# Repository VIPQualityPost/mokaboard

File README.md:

# mokaboard
A custom mechanical keyboard that is suited to my preferences.

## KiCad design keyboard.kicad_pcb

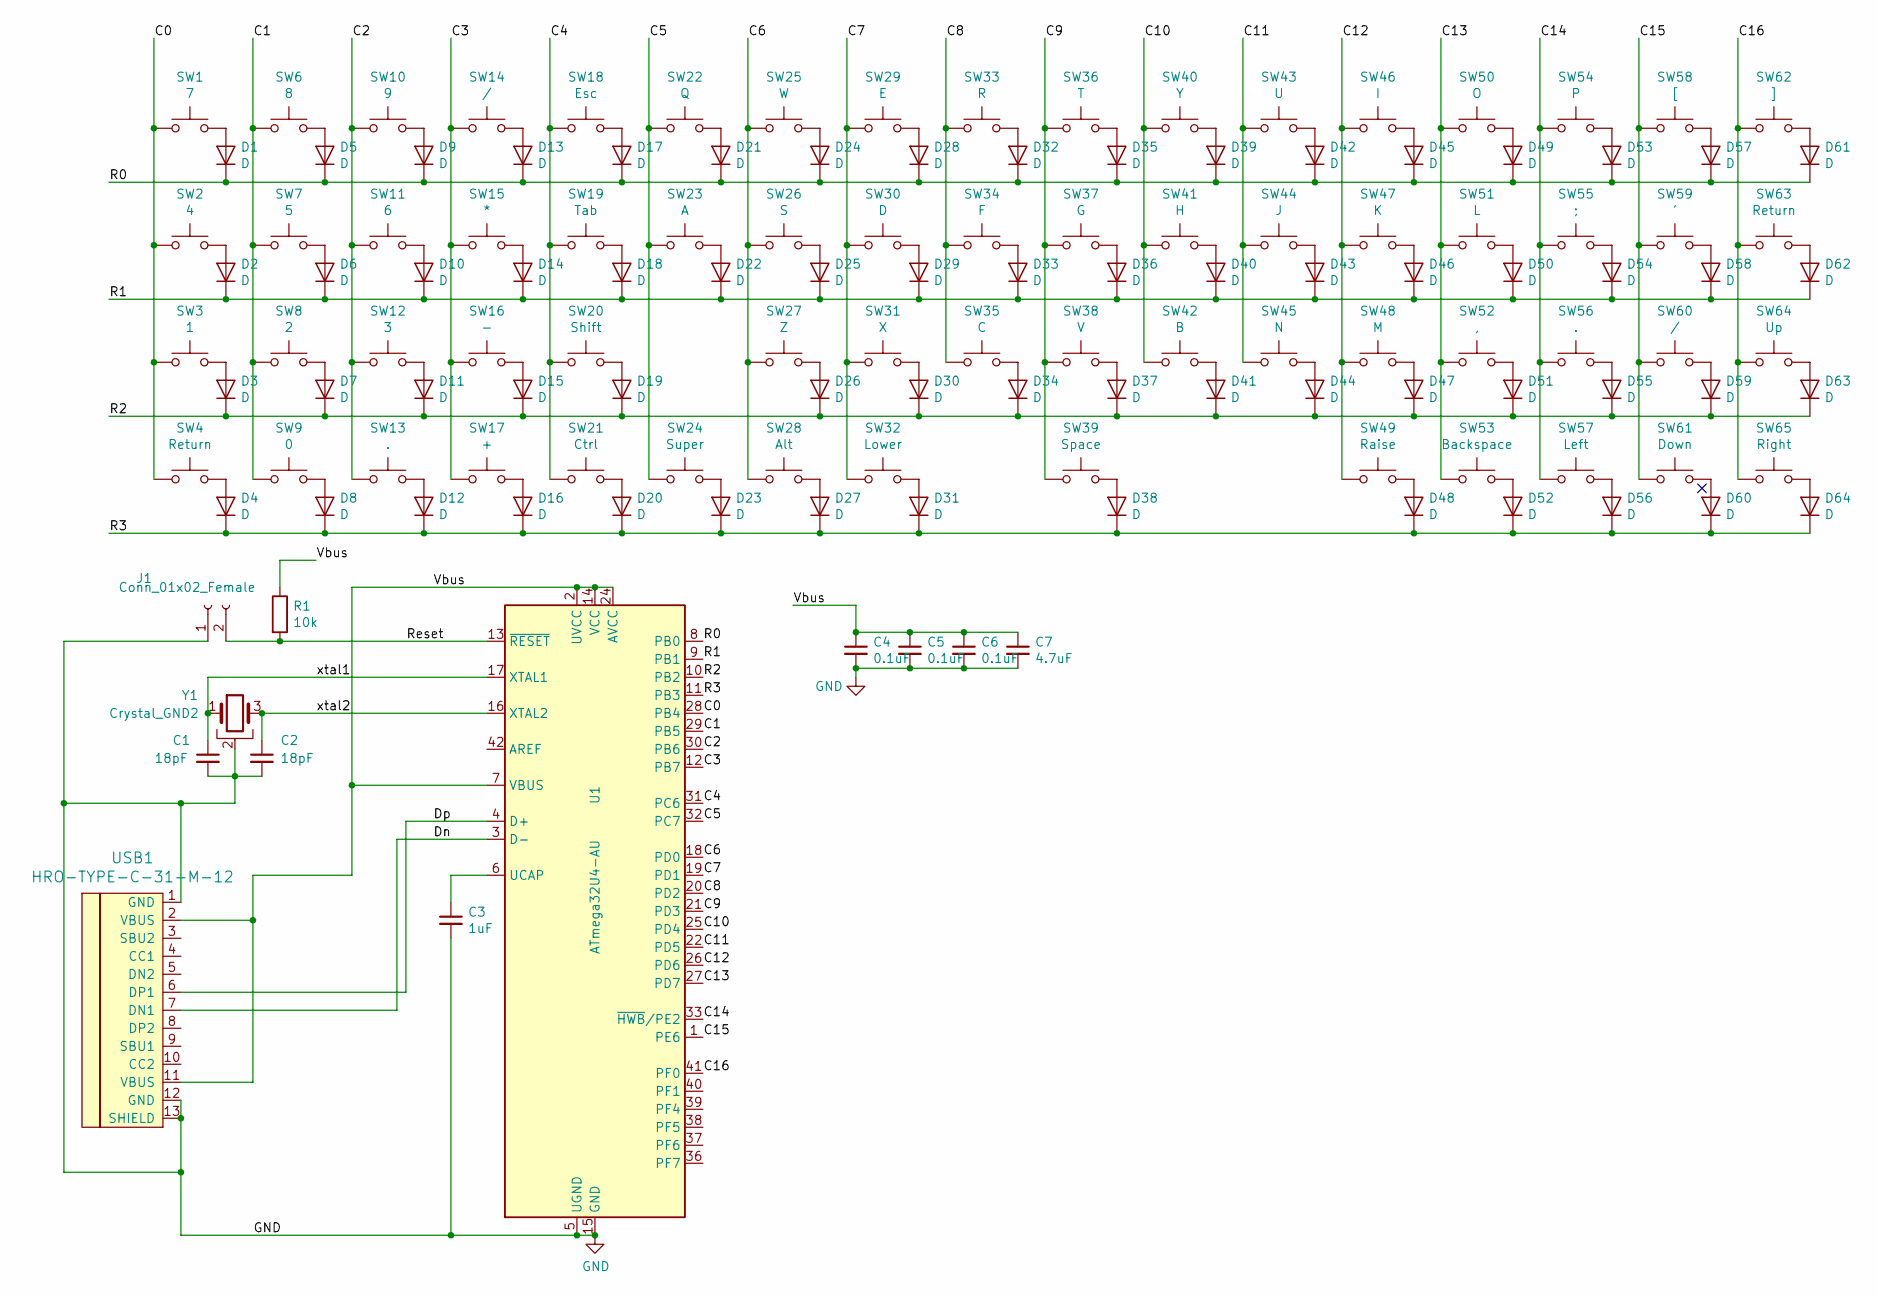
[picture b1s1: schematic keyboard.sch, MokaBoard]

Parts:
C1, C2: 18pF; C_0603_1608Metric_Pad1.05x0.95mm_HandSolder
C3: 1uF; C_0603_1608Metric_Pad1.05x0.95mm_HandSolder
C4, C5, C6: 0.1uF; C_0603_1608Metric_Pad1.05x0.95mm_HandSolder
C7: 4.7uF; C_0603_1608Metric_Pad1.05x0.95mm_HandSolder
D1, D2, D3, D4, D5, D6, D7, D8, D9, D10, D11, D12, D13, D14, D15, D16, D17, D18, D19, D20, D21, D22, D23, D24, D25, D26, D27, D28, D29, D30, D31, D32, D33, D34, D35, D36, D37, D38, D39, D40, D41, D42, D43, D44, D45, D46, D47, D48, D49, D50, D51, D52, D53, D54, D55, D56, D57, D58, D59, D60, D61, D62, D63, D64: D; D_MiniMELF_Handsoldering
J1: Conn_01x02_Female; PinHeader_1x02_P1.27mm_Vertical
R1: 10k; R_0603_1608Metric_Pad1.05x0.95mm_HandSolder
SW1: 7; MX-1U
SW2: 4; MX-1U
SW3: 1; MX-1U
SW4, SW63: Return; MX-1U
SW6: 8; MX-1U
SW7: 5; MX-1U
SW8: 2; MX-1U
SW9: 0; MX-1U
SW10: 9; MX-1U
SW11: 6; MX-1U
SW12: 3; MX-1U
SW13, SW56: .; MX-1U
SW14, SW60: /; MX-1U
SW15: *; MX-1U
SW16: -; MX-1U
SW17: +; MX-1U
SW18: Esc; MX-1U
SW19: Tab; MX-1.25U
SW20: Shift; MX-2U
SW21: Ctrl; MX-1U
SW22: Q; MX-1U
SW23: A; MX-1U
SW24: Super; MX-1U
SW25: W; MX-1U
SW26: S; MX-1U
SW27: Z; MX-1U
SW28: Alt; MX-1U
SW29: E; MX-1U
SW30: D; MX-1U
SW31: X; MX-1U
SW32: Lower; MX-1.25U
SW33: R; MX-1U
SW34: F; MX-1U
SW35: C; MX-1U
SW36: T; MX-1U
SW37: G; MX-1U
SW38: V; MX-1U
SW39: Space; MX-3U
SW40: Y; MX-1U
SW41: H; MX-1U
SW42: B; MX-1U
SW43: U; MX-1U
SW44: J; MX-1U
SW45: N; MX-1U
SW46: I; MX-1U
SW47: K; MX-1U
SW48: M; MX-1U
SW49: Raise; MX-1.25U
SW50: O; MX-1U
SW51: L; MX-1U
SW52: ,; MX-1U
SW53: Backspace; MX-1.75U
SW54: P; MX-1U
SW55: ;; MX-1U
SW57: Left; MX-1U
SW58: [; MX-1U
SW59: '; MX-1U
SW61: Down; MX-1U
SW62: ]; MX-1.25U
SW64: Up; MX-1.25U
SW65: Right; MX-1U
U1: ATmega32U4-AU; TQFP-44_10x10mm_P0.8mm
USB1: HRO-TYPE-C-31-M-12; HRO-TYPE-C-31-M-12-HandSoldering
Y1: Crystal_GND2; Oscillator_SMD_Abracon_ASE-4Pin_3.2x2.5mm_HandSoldering

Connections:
/C0: SW1.1, SW2.1, SW3.1, SW4.1, U1.28 (PB4)
/C1: SW6.1, SW7.1, SW8.1, SW9.1, U1.29 (PB5)
/C2: SW10.1, SW11.1, SW12.1, SW13.1, U1.30 (PB6)
/C3: SW14.1, SW15.1, SW16.1, SW17.1, U1.12 (PB7)
/C4: SW18.1, SW19.1, SW20.1, SW21.1, U1.31 (PC6)
/C5: SW22.1, SW23.1, SW24.1, U1.32 (PC7)
/C6: SW25.1, SW26.1, SW27.1, SW28.1, U1.18 (PD0)
/C7: SW29.1, SW30.1, SW31.1, SW32.1, U1.19 (PD1)
/C8: SW33.1, SW34.1, SW35.1, U1.20 (PD2)
/C9: SW36.1, SW37.1, SW38.1, SW39.1, U1.21 (PD3)
/C10: SW40.1, SW41.1, SW42.1, U1.25 (PD4)
/C11: SW43.1, SW44.1, SW45.1, U1.22 (PD5)
/C12: SW46.1, SW47.1, SW48.1, SW49.1, U1.26 (PD6)
/C13: SW50.1, SW51.1, SW52.1, SW53.1, U1.27 (PD7)
/C14: SW54.1, SW55.1, SW56.1, SW57.1, U1.33 (~HWB~/PE2)
/C15: SW58.1, SW59.1, SW60.1, SW61.1, U1.1 (PE6)
/C16: SW62.1, SW63.1, SW64.1, SW65.1, U1.41 (PF0)
/Dn: U1.3 (D-), USB1.7 (DN1)
/Dp: U1.4 (D+), USB1.6 (DP1)
/R0: D1.1 (K), D5.1 (K), D9.1 (K), D13.1 (K), D17.1 (K), D21.1 (K), D24.1 (K), D28.1 (K), D32.1 (K), D35.1 (K), D39.1 (K), D42.1 (K), D45.1 (K), D49.1 (K), D53.1 (K), D57.1 (K), D61.1 (K), U1.8 (PB0)
/R1: D2.1 (K), D6.1 (K), D10.1 (K), D14.1 (K), D18.1 (K), D22.1 (K), D25.1 (K), D29.1 (K), D33.1 (K), D36.1 (K), D40.1 (K), D43.1 (K), D46.1 (K), D50.1 (K), D54.1 (K), D58.1 (K), D62.1 (K), U1.9 (PB1)
/R2: D3.1 (K), D7.1 (K), D11.1 (K), D15.1 (K), D19.1 (K), D26.1 (K), D30.1 (K), D34.1 (K), D37.1 (K), D41.1 (K), D44.1 (K), D47.1 (K), D51.1 (K), D55.1 (K), D59.1 (K), D63.1 (K), U1.10 (PB2)
/R3: D4.1 (K), D8.1 (K), D12.1 (K), D16.1 (K), D20.1 (K), D23.1 (K), D27.1 (K), D31.1 (K), D38.1 (K), D48.1 (K), D52.1 (K), D56.1 (K), D60.1 (K), D64.1 (K), U1.11 (PB3)
/Reset: J1.2, R1.2, U1.13 (~RESET)
/Vbus: C4.1, C5.1, C6.1, C7.1, R1.1, U1.2 (UVCC), U1.7 (VBUS), U1.14 (VCC), U1.24 (AVCC), U1.34 (VCC), U1.44 (AVCC), USB1.2 (VBUS), USB1.11 (VBUS)
/xtal1: C1.1, U1.17 (XTAL1), Y1.1
/xtal2: C2.1, U1.16 (XTAL2), Y1.3
GND: C1.2, C2.2, C3.2, C4.2, C5.2, C6.2, C7.2, J1.1, U1.5 (UGND), U1.15 (GND), U1.23 (GND), U1.35 (GND), U1.43 (GND), USB1.1 (GND), USB1.12 (GND), USB1.13 (SHIELD), Y1.2
unnamed: C3.1, U1.6 (UCAP)
unnamed: D1.2 (A), SW1.2
unnamed: D2.2 (A), SW2.2
unnamed: D3.2 (A), SW3.2
unnamed: D4.2 (A), SW4.2
unnamed: D5.2 (A), SW6.2
unnamed: D6.2 (A), SW7.2
unnamed: D7.2 (A), SW8.2
unnamed: D8.2 (A), SW9.2
unnamed: D9.2 (A), SW10.2
unnamed: D10.2 (A), SW11.2
unnamed: D11.2 (A), SW12.2
unnamed: D12.2 (A), SW13.2
unnamed: D13.2 (A), SW14.2
unnamed: D14.2 (A), SW15.2
unnamed: D15.2 (A), SW16.2
unnamed: D16.2 (A), SW17.2
unnamed: D17.2 (A), SW18.2
unnamed: D18.2 (A), SW19.2
unnamed: D19.2 (A), SW20.2
unnamed: D20.2 (A), SW21.2
unnamed: D21.2 (A), SW22.2
unnamed: D22.2 (A), SW23.2
unnamed: D23.2 (A), SW24.2
unnamed: D24.2 (A), SW25.2
unnamed: D25.2 (A), SW26.2
unnamed: D26.2 (A), SW27.2
unnamed: D27.2 (A), SW28.2
unnamed: D28.2 (A), SW29.2
unnamed: D29.2 (A), SW30.2
unnamed: D30.2 (A), SW31.2
unnamed: D31.2 (A), SW32.2
unnamed: D32.2 (A), SW33.2
unnamed: D33.2 (A), SW34.2
unnamed: D34.2 (A), SW35.2
unnamed: D35.2 (A), SW36.2
unnamed: D36.2 (A), SW37.2
unnamed: D37.2 (A), SW38.2
unnamed: D38.2 (A), SW39.2
unnamed: D39.2 (A), SW40.2
unnamed: D40.2 (A), SW41.2
unnamed: D41.2 (A), SW42.2
unnamed: D42.2 (A), SW43.2
unnamed: D43.2 (A), SW44.2
unnamed: D44.2 (A), SW45.2
unnamed: D45.2 (A), SW46.2
unnamed: D46.2 (A), SW47.2
unnamed: D47.2 (A), SW48.2
unnamed: D48.2 (A), SW49.2
unnamed: D49.2 (A), SW50.2
unnamed: D50.2 (A), SW51.2
unnamed: D51.2 (A), SW52.2
unnamed: D52.2 (A), SW53.2
unnamed: D53.2 (A), SW54.2
unnamed: D54.2 (A), SW55.2
unnamed: D55.2 (A), SW56.2
unnamed: D56.2 (A), SW57.2
unnamed: D57.2 (A), SW58.2
unnamed: D58.2 (A), SW59.2
unnamed: D59.2 (A), SW60.2
unnamed: D60.2 (A), SW61.2
unnamed: D61.2 (A), SW62.2
unnamed: D62.2 (A), SW63.2
unnamed: D63.2 (A), SW64.2
unnamed: D64.2 (A), SW65.2

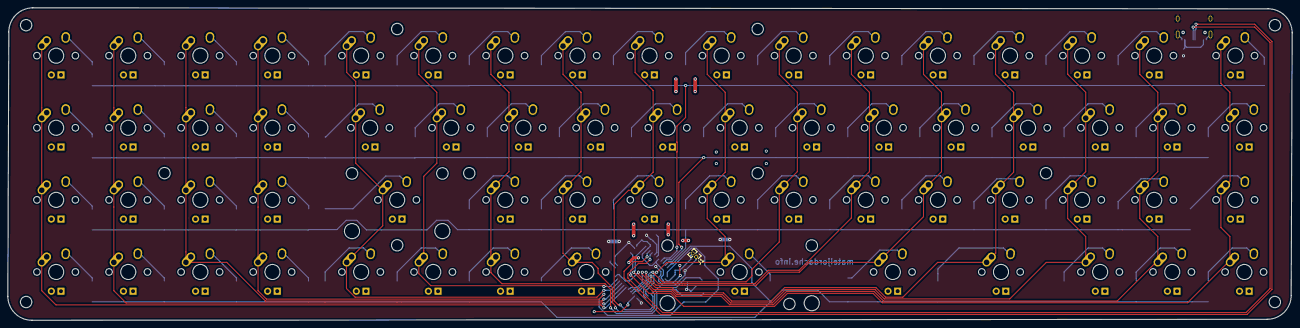
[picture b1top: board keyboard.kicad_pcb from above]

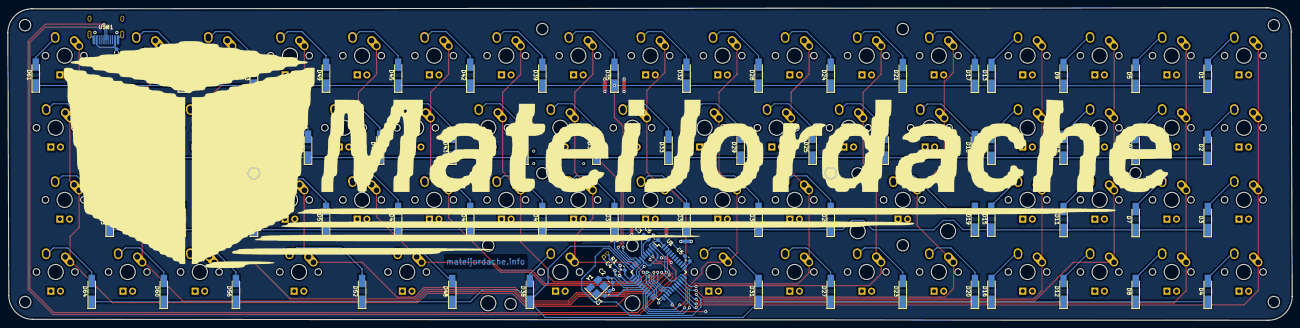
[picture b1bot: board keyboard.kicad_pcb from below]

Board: 2 copper layers, 339.3 x 82.5 mm, 140 parts (75 on the bottom side), 93 nets.
